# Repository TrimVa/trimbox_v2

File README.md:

# TrimBox

Enregistreur de télémétrie **GPS + inertiel** pour voitures radiocommandées,
avec **chronométrage au tour** affiché et annoncé sur la radio, **console web**
d'analyse et **mise à jour par Wi-Fi**. Construit autour d'un **ESP32-S3**.

> **État :** firmware **2.0-a17**, console **1.7.18**. Tout est écrit et testé
> sur PC, dans un navigateur et dans un émulateur ESP32-S3. **Essais sur le
> vrai matériel en cours** : GPS, IMU et script Lua sur la MT12 validés ; reste
> le roulage. Voir [les bancs d'essai](#bancs-dessai-à-la-réception-du-matériel).

---

## Sommaire

1. [Ce que fait le module](#ce-que-fait-le-module)
2. [Matériel](#matériel)
3. [Câblage](#câblage)
4. [Mise en route](#mise-en-route)
5. [Utilisation au bord de la piste](#utilisation-au-bord-de-la-piste)
6. [Console web](#console-web)
7. [Radio MT12 et script Lua](#radio-mt12-et-script-lua)
8. [Mises à jour du firmware](#mises-à-jour-du-firmware)
9. [Personnalisation](#personnalisation)
10. [Moniteur série et DEL](#moniteur-série-et-del)
11. [Sécurité et robustesse](#sécurité-et-robustesse)
12. [Dépannage](#dépannage)
13. [Contenu du dépôt](#contenu-du-dépôt)
14. [Compilation et tests automatiques](#compilation-et-tests-automatiques)
15. [Limites connues et suite du projet](#limites-connues-et-suite-du-projet)
16. [Documentation](#documentation)

---

## Ce que fait le module

| Fonction | Détail |
|---|---|
| **Enregistrement autonome** | GPS à 25 Hz + accéléromètre et gyroscope, sur la mémoire interne de 16 Mo. Aucun téléphone nécessaire pendant le roulage. |
| **Autonomie mémoire** | **01h42min à 25 Hz**, 02h08min à 20 Hz, 04h17min à 10 Hz, 08h34min à 5 Hz, 42h52min à 1 Hz (154 333 points). |
| **Enregistrement automatique** | l'enregistrement s'ouvre tout seul dès que la voiture roule et se ferme après 30 s à l'arrêt : **un roulage = une session**, sans rien toucher. Réglable, ou remplaçable par les boutons de la console. |
| **Filtres d'enregistrement** | attente du GPS, pause sans signal, extinction après inactivité. Rien n'est stocké au stand. |
| **Chrono embarqué** | calculé dans le module à 25 Hz, temps interpolés entre deux mesures (précision de l'ordre de la milliseconde). Mode **circuit** (une ligne, un temps par tour) ou **dragster** (départ + arrivée, chronos 0-30 / 0-50 / 0-80 km/h et 25 / 50 / 100 m). |
| **Pose de ligne depuis la radio** | voiture **arrêtée sur la ligne** : la commande arme la ligne, qui est posée dans le sens du départ dès que la voiture démarre (dans les 10 s) ; ce départ compte. Voiture **lancée** : la ligne est posée là où passe la voiture, perpendiculaire à sa trajectoire. Conservée d'une session à l'autre. |
| **Télémétrie radio** | position GPS, vitesse, état, et un message par tour (temps + écart au meilleur) vers la MT12, qui **annonce les temps à voix haute**. |
| **Console Bluetooth** | depuis la page GitHub du projet, sur Chrome Android. Comme le Wi-Fi, le Bluetooth se coupe quand la voiture roule et revient 30 s après l'arrêt. |
| **Console Wi-Fi** | le module ouvre son propre réseau quand la voiture est arrêtée depuis 30 s, et le coupe dès qu'elle roule. Fonctionne aussi sur **iPhone**, sans Internet. |
| **Analyse** | tracé coloré par vitesse, zoom, tours et parcours, forces G, temps en l'air, statistiques au survol du tracé, comparaison de sessions (portion choisie en glissant sur le profil, statistiques par session). Les **lignes posées depuis la radio** sont reprises d'office, et les **tours calculés en course** par le module s'affichent à côté de ceux de la console. |
| **Exports** | VBO (RaceChrono, Circuit Tools), CSV, GPX ; import de ces mêmes formats. |
| **Mise à jour Wi-Fi** | depuis le téléphone, avec retour automatique à la version précédente si la nouvelle ne démarre pas correctement. |

---

## Matériel

| Élément | Référence utilisée | Rôle |
|---|---|---|
| Carte | **NiceMCU « ESP32-S3_MINI_Nano » N16R8** | 16 Mo de flash, 8 Mo de PSRAM, Bluetooth, Wi-Fi, une prise USB-C |
| GPS | **HGLRC M100 Mini** (u-blox M10) | position et vitesse à 25 Hz |
| Centrale inertielle | module **LSM6DS3 / LSM6DS3TR-C** (I2C) | accélérations ±16 g, rotations ±2000 °/s |
| Récepteur | **RadioMaster ER5C-i** (ExpressLRS 2,4 GHz) | commande de la voiture + liaison CRSF avec le module |
| Radio | **RadioMaster MT12** (EdgeTX) | affichage du chrono, pose des lignes |
| ESC | **XC-E8** | aucune liaison : son port X-Bus est une entrée (voir ci-dessous) |
| Alimentation | régulateur abaisseur **5 V, ≥ 1 A** | depuis le BEC de l'ESC (6 à 8,4 V) |

Au banc, l'USB de la carte suffit à tout alimenter (à vérifier : la broche VIN
doit recevoir le 5 V de l'USB, sinon le GPS reste éteint).

⚠️ **Le module ne pilote jamais la voiture.** Direction et ESC restent sur
les sorties du récepteur : si le module plante, la voiture reste pilotable.

---

## Câblage

Schéma vectoriel : [SVG](docs/cablage-trimbox-s3.svg) · [PDF à imprimer](docs/cablage-trimbox-s3.pdf) (régénéré par `tools/gen_cablage.py`).

| Module | Broche du module | Carte (sérigraphie au dos) |
|---|---|---|
| **GPS M100 Mini** | V | **VIN** (5 V) |
| | G | GND |
| | T (TX) | **IO18** |
| | R (RX) | **IO17** |
| **IMU LSM6DS3** | VCC | **3V3** |
| | GND | GND |
| | SDA | **IO8** |
| | SCL | **IO9** |
| **Récepteur ER5C-i** | sortie 2 (Serial TX) | **IO16** |
| | sortie 3 (Serial RX) | **IO15** |
| | − | GND |
| **Alimentation (voiture)** | régulateur 5 V | **VIN** + GND |

**Boîtier imprimé 3D (1/10)** : [docs/boitier/trimbox-boitier.3mf](docs/boitier/trimbox-boitier.3mf),
sans aucune vis : carte clipsée dans le fond, GPS (antenne à l'air libre par
une ouverture) et IMU clipsés dans le couvercle, trou pour voir la DEL, dessous
plat pour adhésif double face + passants pour colliers. Mesures, impression et montage : [docs/boitier/LISEZMOI.md](docs/boitier/LISEZMOI.md).

Réglages du récepteur (interface web de l'ER5C-i, onglet *Model*) :
sorties 2 et 3 en **Serial TX / RX, protocole CRSF** ; direction sur la
sortie 1 (CH1) ; ESC sur la sortie 4 (**CH2**).

Règles à respecter :

- **Jamais plus de 3,3 V sur une broche GPIO** : l'ESP32-S3 ne tolère pas le 5 V.
- **Jamais le BEC (6 à 8,4 V) directement sur la broche VIN** de la carte :
  toujours passer par le régulateur 5 V.
- Broches à ne pas utiliser : IO33 à IO37 (mémoire PSRAM, bien que sorties sur la carte), 19 et 20 (USB),
  0, 3, 45, 46 (démarrage).
- L'IMU se visse **rigidement** sur le châssis, près du centre de gravité,
  axes alignés sur la voiture (pas sur mousse).

---

## Mise en route

Détail pas à pas : **[DEMARRAGE.md](DEMARRAGE.md)**. En résumé :

1. **Envoyer ce dépôt sur GitHub.** L'onglet **Actions** compile et teste
   tout seul (10 à 15 min la première fois).
2. **Activer GitHub Pages** (*Settings → Pages → branche `main`, dossier
   `/ (root)`*) pour la console Bluetooth en ligne.
3. **Premier flash, une seule fois, par câble depuis un ordinateur** :
   page **Releases** du dépôt → dernière version → `trimbox_s3-complet.bin`, avec
   https://espressif.github.io/esptool-js/ (Chrome ou Edge), adresse **0x0**,
   prise **USB** de la carte.
4. **Vérifier** : 30 s après la mise sous tension, le Wi-Fi
   `TrimBox-Buggy-1` apparaît (mot de passe `trimbox-rc`, à changer dans
   *Réglages → Véhicule et point d'accès*) ; http://192.168.4.1/
   affiche la console et la version du firmware en haut à droite.
5. **Radio** : copier `lua/trmbox.lua` sur la MT12 et régler le mixage de CH8
   ([lua/LISEZMOI.md](lua/LISEZMOI.md)).

---

## Utilisation au bord de la piste

1. **Brancher la batterie de la voiture.** Le module démarre toujours
   **enregistrement arrêté**.
2. **Rien à faire** : l'enregistrement démarre tout seul dès que la voiture
   roule (au-dessus du seuil d'arrêt, 5 km/h par défaut) et se ferme après
   30 s à l'arrêt. Chaque roulage donne une session. Les boutons *Démarrer*
   et *Arrêter* de la console restent disponibles, et la case **Démarrer et
   arrêter tout seul** permet de revenir à la commande manuelle.
3. **Rouler.** Le Wi-Fi **et le Bluetooth** du module se coupent dès que la
   voiture dépasse 7 km/h, pour ne pas gêner la radio ; ils reviennent seuls
   30 s après l'arrêt.
4. **Poser la ligne** (une fois par piste) : voiture **arrêtée sur la ligne**,
   sur la MT12 page *Lignes*, molette sur « Poser DEPART », **ENT**, puis
   **démarrer dans les 10 s** : la ligne est posée dans le sens du départ, et
   ce départ compte déjà. En roulant (> 7 km/h), la même commande pose la
   ligne tout de suite, là où passe la voiture.
5. **Chaque tour** : la radio annonce le temps ; double bip aigu avant
   l'annonce s'il s'agit du meilleur tour.
6. **Au stand** : 30 s après l'arrêt de la voiture, le Wi-Fi revient. Le
   téléphone s'y reconnecte, la console aussi : **télécharger** la session,
   analyser, exporter.

Mode **dragster** : poser aussi la ligne d'**arrivée** (« Poser ARRIVEE »).
Un temps par passage départ → arrivée, plus les chronos intermédiaires.

---

## Console web

Un seul fichier (`index.html`), sans aucune dépendance : elle fonctionne sans
réseau. Trois sources de données, au choix en haut de page :

| Source | Quand | Adresse |
|---|---|---|
| **Bluetooth** | Chrome sur Android, ordinateur | `https://<pseudo>.github.io/<dépôt>/` |
| **Wi-Fi** | tout téléphone, dont iPhone ; au stand | `http://192.168.4.1/` (Wi-Fi du module) |
| **Démo** | sans matériel, pour découvrir | `…/index.html?demo=1` |

Fonctions : données en direct, état de la mémoire, démarrage / arrêt et
réglages de l'enregistrement, téléchargement et effacement, analyse
(tracé, tours, dragster, G, sauts), comparaison, exports VBO / CSV / GPX,
mise à jour du firmware (en Wi-Fi), thème clair / sombre et **couleur
d'accent** au choix (bouton palette), installable comme une application
(PWA). L'en-tête affiche la version de la console et celle du firmware de la
carte connectée.

La mise en page s'adapte à l'écran : une colonne sur téléphone (dès 320 px),
une colonne plus large sur tablette. Sur ordinateur, la console occupe **toute
la largeur** avec des **onglets** *Appareil*, *Analyse*, *Sessions* et
*Réglages* ; dans chaque onglet, les panneaux se partagent la ligne.

**Fond satellite en Wi-Fi.** Le point d'accès de la TrimBox n'a pas
Internet : les images satellite passent par la **4G du téléphone**. Pour cela :

- sur Android, activez les **données mobiles quand le Wi-Fi n'a pas
  Internet** (option « Basculer vers les données mobiles » ou « Wi-Fi
  adaptatif », selon la marque) ;
- ouvrez la console dans **Chrome** (`http://192.168.4.1`), et non dans la
  fenêtre « Se connecter à TrimBox-… » qui s'ouvre toute seule : cette
  fenêtre est limitée au Wi-Fi, les images ne peuvent pas y arriver.

Sans réponse d'Internet, la console garde le fond satellite actif, affiche une
explication et réessaie toutes les 10 s : la carte apparaît dès que la 4G
répond. Le reste fonctionne à l'identique, et le téléchargement est bien plus
rapide qu'en Bluetooth. Sans réseau mobile, deux solutions :

- **après la séance** : télécharger la session (CSV / GPX / VBO), puis la
  rouvrir dans la console en ligne, avec *Ouvrir des enregistrements* ;
- **au bord de la piste** : utiliser la console en ligne connectée **par
  Bluetooth**.

**Voiture à l'arrêt.** Une voiture posée semble « dériver » de 1 à 3 m à cause
du bruit du GPS. Pour l'éviter, le firmware fige la position et met la
vitesse à 0 dès que la voiture est immobile :
- **quand** : vitesse sous 1,1 km/h pendant 0,2 s, sans mouvement vu par l'IMU ;
- **reprise** : dès que la vitesse dépasse 2,2 km/h, que l'IMU bouge, ou que la
  voiture s'est éloignée de 4 m ;
- **pour enregistrer le GPS brut** : `STILL_HOLD 0` dans `config.h`.

---

## Radio MT12 et script Lua

Script `lua/trmbox.lua` → carte SD de la radio, `SCRIPTS/TELEMETRY/`.
Mode d'emploi complet : **[lua/LISEZMOI.md](lua/LISEZMOI.md)**.

- **Page Chrono** : dernier tour en grand, numéro, écart, meilleur tour,
  tours précédents ; état du module, lignes posées, indicateur Wi-Fi.
- **Page Machine** : vitesse (0 sous 3 km/h), vitesse maximale, satellites,
  qualité de liaison, RSSI, altitude, **tension de la batterie** (capteur du
  récepteur) et **date et heure du GPS** en heure locale.
- **Page Lignes** : poser le départ, l'arrivée, effacer.
- **Mixage CH8, indispensable** : *Modèle → Mixeur → CH8*, source **MAX**,
  poids **GV9**, mode « ajouter ». Sans lui, aucune commande de pose ne part
  de la radio. La page *Lignes* affiche la valeur réelle de la voie (`CH8
  +0%`), qui doit passer à ±100 % pendant un envoi. Un inter 3 positions sur
  CH8 marche aussi sans le script (haut 0,5 s = départ, bas 0,5 à 3 s =
  arrivée, bas 3 s = effacement).
- **Réglage ExpressLRS** : *Telem Ratio* **1:16** ou plus fréquent, sinon
  des messages de tour peuvent manquer.
- **Annonces vocales** : « meilleur tour », le temps du tour, l'écart avec le
  tour précédent (« moins 0,35 », « plus 1,00 », « égal »), et les accusés
  de pose de ligne (« départ posé », « vitesse trop faible »…). Les nombres
  viennent du pack vocal de la radio ; les 12 mots du script sont fournis dans
  `lua/SOUNDS/trimbox/` (copier `lua/SOUNDS` à la racine de la carte SD). Ils
  ont été produits par `tools/sons/generer-voix.bat` avec la voix Azure du pack
  EdgeTX (liste : `tools/sons/liste-sons-mt12.csv`). Sans eux, des bips les
  remplacent. `tools/sons/generer-mot.bat` produit à la demande d'autres mots
  ou phrases avec la même voix (texte et nom demandés, écoute avant d'enregistrer).
- **Date et heure GPS** : le module envoie la trame CRSF `0x03` une fois par
  seconde. Il faut **ExpressLRS 4.1 ou plus récent** sur l'émetteur **et** sur
  le récepteur pour qu'elle soit relayée, et une version d'EdgeTX qui la
  décode : après *Découvrir les capteurs*, un capteur **`Date`** apparaît.
  Avec l'option *Ajuster l'horloge* de ce capteur, la radio se met à l'heure
  toute seule. Le script affiche l'heure locale (France par défaut, heure
  d'été automatique ; réglages `TZ_OFFSET` et `TZ_EU_DST`).

Messages envoyés à la radio (capteur `FM`) :

| Message | Sens |
|---|---|
| `L12 21.345+0.35` | tour 12 en 21,345 s, 0,35 s de plus que le meilleur |
| `S REC C` | état (REC / PAUSE / STOP / NOFIX) et lignes (C circuit, D dragster, - aucune) |
| `R 0-50 2.184` | chrono intermédiaire (dragster) |
| `K DEPART OK` | accusé de pose de ligne (ou `VIT FAIBLE`, `PAS DE FIX`, `EFFACE`) |
| `W WIFI ON` | Wi-Fi de la console allumé / coupé |
| `U MAJ OK` | étapes d'une mise à jour du firmware |

---

## Mises à jour du firmware

**Par Wi-Fi, sans ordinateur :**

1. Modifier le code dans GitHub (bouton crayon) et valider : la compilation
   repart seule.
2. Page **Releases** du dépôt → dernière version → `trimbox_s3-app.bin`
   (publiée automatiquement quand tout est vert et que `FIRMWARE_VER` a
   changé ; sinon *Actions* → compilation verte → artefact
   **firmware-s3-app**).
3. Voiture **et** enregistrement arrêtés : console Wi-Fi → **Mise à jour du
   firmware** → choisir le fichier → **Envoyer au module** (environ 10 s).
4. La console se reconnecte et affiche « ✓ Nouvelle version active ».

Filets de sécurité :

- mauvais fichier refusé avec un message clair (fichier « complet », .uf2
  de la v1, autre projet, image corrompue) ;
- l'ancienne version n'est jamais effacée pendant l'envoi ;
- la nouvelle version ne se **valide qu'après 15 s** de bon fonctionnement ;
  si elle plante ou se fige avant, le module **revient seul** à la
  précédente ;
- page de secours : http://192.168.4.1/update.

⚠️ `trimbox_s3/partitions.csv` ne doit **jamais** changer dans une mise à jour
Wi-Fi : la table de partitions ne se remplace que par câble.

---

## Personnalisation

Dans **`trimbox_s3/src/config.h`** :

| Réglage | Par défaut | Rôle |
|---|---|---|
| `DEVICE_NICKNAME` | `"Buggy 1"` | nom du véhicule **par défaut** (16 caractères max) : `TrimBox Buggy 1` en Bluetooth, `TrimBox-Buggy-1` en Wi-Fi ; se change ensuite dans la console |
| `WIFI_PASS` | `"trimbox-rc"` | mot de passe Wi-Fi **par défaut** (8 à 63 caractères) ; se change dans la console |
| `WIFI_AUTO_DEFAULT` | `1` | Wi-Fi automatique à l'arrêt (0 : seulement à la demande) |
| `WIFI_AUTO_ON_S` | `30` | secondes d'arrêt avant l'ouverture du Wi-Fi |
| `CRSF_LINE_CHANNEL_DEFAULT` | `8` | voie radio de pose de ligne |
| `PIN_LED_RGB` | `48` | DEL RGB de la carte (à confirmer : si elle reste éteinte, essayer 38 ou 21) |
| `AXIS_*` | capteur à plat, x vers l'avant | orientation de l'IMU selon son montage |

Les autres valeurs du fichier ont été fixées par mesure ou par contrainte
matérielle : ne pas les modifier sans raison (voir les cahiers des charges).

Plusieurs voitures : un nom de véhicule différent par module suffit à les
distinguer (Bluetooth, Wi-Fi et console). Il se change dans la console,
*Réglages → Véhicule et point d'accès*, sans recompiler.

---

## Moniteur série et DEL

Moniteur série à **115 200 bauds**, sur la prise **USB** de la carte
(onglet *Console* d'esptool-js, moniteur de l'IDE Arduino, PuTTY…) :

| Touche | Effet |
|---|---|
| `s` | arrêt d'urgence de l'enregistrement |
| `r` | démarrer l'enregistrement (essai sans téléphone) |
| `w` | Wi-Fi marche / arrêt |
| `i` | état : mémoire, enregistrement, configuration, lignes |
| `b` | banc d'essai : cadence GPS, IMU, radio, Bluetooth, Wi-Fi, partition du firmware |
| `m` | mesures de la centrale inertielle en direct (10 lignes, mg et c°/s) |
| `z` | configuration par défaut (données conservées) |
| `x` | nom du véhicule et mot de passe Wi-Fi d'origine (mot de passe oublié) |
| `?` | aide |

**Bouton BOOT**, appui long de 3 s : Wi-Fi marche / arrêt.

**DEL de la carte :**

| Couleur | Sens |
|---|---|
| rouge clignotant | GPS ou mémoire absents (normal au banc sans GPS) |
| rouge fixe | enregistrement en cours |
| orange | enregistrement en pause |
| vert clignotant | GPS calé, prêt |
| bleu fixe | console connectée |
| bleu clignotant | Wi-Fi ouvert, en attente du téléphone |

Les couleurs se superposent : rouge + bleu = violet (enregistrement en cours, console connectée).

---

## Sécurité et robustesse

- **Coupure d'alimentation** (batterie arrachée en pleine session) : les
  données déjà enregistrées restent intactes et téléchargeables ; la
  configuration est écrite en double exemplaire ; l'enregistrement **ne
  reprend jamais tout seul** au redémarrage ; les points incomplets sont
  écartés à la lecture.
- **Effacement de la mémoire** : impossible pendant un enregistrement, et
  non annulable une fois lancé (il ne dure que quelques secondes).
- **Wi-Fi et Bluetooth coupés en roulant**, quel que soit le réglage : la
  liaison de commande 2,4 GHz passe avant la console. Rallumage automatique
  après 30 s d'arrêt (`BLE_AUTO_OFF 0` dans `config.h` pour garder le
  Bluetooth en permanence).
- **Chien de garde** : si le programme se fige plus de 5 s, la carte
  redémarre seule.
- **Protocole** : trames avec somme de contrôle, réassemblage tolérant aux
  pertes ; une trame corrompue ne peut pas produire de valeurs absurdes
  dans l'analyse.

---

## Dépannage

| Problème | Piste |
|---|---|
| Carte non détectée pour le flash | câble de **données**, prise **USB** ; BOOT maintenu + RST, relâcher BOOT |
| Pas de Wi-Fi `TrimBox-…` | attendre 30 s voiture arrêtée ; appui long BOOT ; touche `w` ; vérifier le journal série |
| « Pas d'accès Internet » sur le téléphone | normal : rester connecté et ouvrir http://192.168.4.1/ |
| `[gnss] AUCUNE RÉPONSE` | TX et RX croisés (GPS TX → GPIO 18), alimentation 5 V |
| GPS à moins de 25 Hz | normal à l'intérieur ; si Galileo est coupé tout seul, le noter (réglage automatique) |
| `[imu] ABSENTE` | SDA = 8, SCL = 9, 3,3 V, masse |
| Radio : « PAS DE LIAISON » | récepteur : sorties 2/3 en CRSF, TX/RX croisés ; *Découvrir les capteurs* sur la MT12 |
| Des tours manquent sur la radio | *Telem Ratio* ExpressLRS trop bas : 1:16 ou plus fréquent |
| Rien ne se passe à la pose de ligne (la page *Lignes* affiche `CH8 +0%`) | mixage CH8 absent : *Modèle → Mixeur → CH8*, source MAX, poids GV9, mode Ajouter |
| « délai dépassé » après une pose à l'arrêt | démarrer dans les 10 s qui suivent la commande |
| Mise à jour refusée | lire le message : enregistrement en cours, mauvais fichier, voiture en mouvement |
| Console : ancienne version affichée | recharger la page ; en Bluetooth, vider le cache du navigateur |
| La compilation GitHub échoue | ouvrir l'étape en rouge dans *Actions* ; le premier test en échec indique la cause |

---

## Contenu du dépôt

```
trimbox_s3/                      firmware ESP32-S3 (croquis Arduino)
│   trimbox_s3.ino               point d'entrée
│   partitions.csv               table de partitions 16 Mo — NE PAS MODIFIER
│   LISEZMOI.md                  câblage, premier flash, bancs d'essai
└── src/
    ├── config.h                 réglages et brochage
    ├── app.cpp                  boucle principale, commandes, chrono, Wi-Fi auto
    ├── console_gz.h             console intégrée (générée, ne pas éditer)
    ├── core/                    logique SANS matériel, testée sur PC :
    │                            protocoles (TrimBox, UBX, CRSF), chrono,
    │                            automate d'enregistrement, pose de ligne,
    │                            configuration A/B, serveur HTTP/WebSocket,
    │                            contrôle des mises à jour
    └── hw/                      pilotes : GPS, IMU, mémoire, Bluetooth,
                                 Wi-Fi, radio, mise à jour
lua/trmbox.lua                   script de télémétrie MT12 (+ LISEZMOI.md)
lua/SOUNDS/trimbox/              les 12 mots des annonces vocales (à copier sur la carte SD)
index.html                       console web (GitHub Pages et firmware)
trimbox-sw.js                    service worker (console hors ligne)
trimbox-diy-console-demo.html    redirection des anciens liens vers la démo
tools/embed_console.py           intègre index.html au firmware
tools/gen_cablage.py             génère le schéma de câblage (docs/)
tools/gen_boitier.py             génère le boîtier imprimé 3D (docs/boitier/)
tools/imu_test/                  croquis de test de la centrale inertielle seule
docs/                            schéma de câblage (SVG, PDF) et boîtier 3D
tools/sons/                      sons de la radio : liste (CSV) + génération Azure des mots du script
tools/xbus_probe/                sonde ESP32 du port X-Bus (piste close)
tests/native/                    tests de la logique (g++) + comparaison avec la console
tests/web/                       console dans un navigateur, avec le serveur du firmware
tests/lua/                       script Lua avec l'API EdgeTX simulée
tests/qemu/                      firmware complet dans l'émulateur ESP32-S3
.github/workflows/build-s3.yml   compilation et tests à chaque envoi
CAHIER-DES-CHARGES.md            spécification complète (matériel, protocole, firmware, radio, console, pièges)
trimbox-etat-projet.json         état du projet, pour reprendre avec une IA
REPRISE-IA.md                    marche à suivre pour reprendre le développement avec une IA
```

---

## Compilation et tests automatiques

À chaque envoi sur GitHub, l'onglet **Actions** enchaîne :

| Étape | Vérifie |
|---|---|
| Tests natifs | protocoles, chrono (bancs v1 : 5 tours de 20,00 s, ligne en 4 endroits ; dragster à 6 m/s²), automate d'enregistrement, pose de ligne, configuration A/B, serveur web, contrôles de mise à jour — plus de 950 vérifications |
| Chrono firmware = console | les mêmes trajets rejoués dans les deux : écart maximal 1 ms |
| Script Lua | messages, sons, impulsions GV9, affichage (API EdgeTX simulée) |
| Compilation | ESP32-S3, core `esp32:esp32@3.3.12`, NimBLE-Arduino 2.5.1 (versions figées) |
| Console dans un navigateur | chargement, connexion Wi-Fi, direct, téléchargement, reconnexion, couleur, envoi du firmware compilé |
| Émulateur | Wi-Fi automatique à l'arrêt, pose de ligne par le script Lua, tours de 12,000 s reçus sans perte, coupure d'alimentation, retour arrière après une mise à jour qui plante |

Artefacts produits :

| Artefact | Contenu | Usage |
|---|---|---|
| `firmware-s3-complet` | `trimbox_s3-complet.bin` (+ fichiers séparés) | premier flash, par câble, adresse 0x0 |
| `firmware-s3-app` | `trimbox_s3-app.bin` | mise à jour par Wi-Fi |
| `capture-console-wifi` | capture d'écran | contrôle visuel de la console |

Il faut être **connecté à GitHub** pour télécharger un artefact.

**Release automatique** : sur la branche `main`, quand tous les jobs sont
verts et que `FIRMWARE_VER` (`trimbox_s3/src/config.h`) n'a pas encore été
publiée, le job *Publication* crée la release `firmware-<version>` : les deux
`.bin`, bootloader et partitions séparés, la console `index.html`, le pack
radio `trimbox-radio.zip`, `SHA256SUMS.txt`, et des notes complètes (usage de
chaque fichier, procédures, nouveautés depuis la release précédente,
empreintes). Téléchargeable **sans compte GitHub**. Une version déjà publiée
n'est jamais écrasée : incrémenter `FIRMWARE_VER` pour publier.

---

## Limites connues et suite du projet

- **Essais matériels en cours** : GPS validé sur la carte (fix 3D,
  13 satellites, ~20 Hz), IMU validée avec `tools/imu_test` (|a| = 0,99 g au
  repos), script Lua validé sur la MT12 (affichage, tours, annonces vocales,
  accusés de pose). Restent à valider : mixage CH8 et pose de ligne depuis la
  radio, enregistrement automatique et chrono en roulage, Bluetooth et Wi-Fi
  en conditions réelles, boîtier imprimé.
- **ESC XC-E8, abandonné** : son port X-Bus (paramètre *PLine* de
  l'application) est une **entrée**. Analyseur logique et sonde ESP32 l'ont
  confirmé : ligne tenue en haut par une résistance de tirage, aucune
  émission, aucune réponse à une poignée de main. Les autres choix de *PLine*
  (Max.Brake, Max.Rev, Acc, DragBrake) sont eux aussi des entrées, et
  *ProtocolId* n'est qu'un numéro d'appareil sur le bus. Il n'y a donc pas de
  télémétrie à lire sur cette prise. La tension de batterie remonte déjà par
  la radio. Détail des essais : cahier des charges §13.
- **Batterie** : la tension s'affiche sur la radio (capteur du récepteur), pas
  dans la console (octet batterie toujours à 0).
- **Premier flash** : nécessite un ordinateur, une seule fois.

### Bancs d'essai à la réception du matériel

Dans l'ordre, en notant la sortie de la touche `b` à chaque étape
(détail dans [trimbox_s3/LISEZMOI.md](trimbox_s3/LISEZMOI.md)) :

1. carte seule : démarrage, mémoire, Wi-Fi, console ;
2. + GPS, dehors : 25 Hz — ✅ fix 3D, 13 satellites, ~20 Hz ;
3. + IMU : capteur reconnu — ✅ avec `tools/imu_test` ;
4. + récepteur : liaison CRSF, capteurs découverts sur la MT12 — ✅ messages
   du chrono reçus par le script Lua ;
5. console : connexion, enregistrement, téléchargement, effacement ;
6. roulage : pose de ligne, tours sur la radio, comparaison avec la console.

---

## Documentation

| Document | Contenu |
|---|---|
| [DEMARRAGE.md](DEMARRAGE.md) | mise en ligne, premier flash, mises à jour |
| [trimbox_s3/LISEZMOI.md](trimbox_s3/LISEZMOI.md) | câblage, flash, moniteur série, bancs d'essai |
| [lua/LISEZMOI.md](lua/LISEZMOI.md) | installation du script, mixage, utilisation |
| [CAHIER-DES-CHARGES.md](CAHIER-DES-CHARGES.md) | spécification complète du projet : matériel, protocole, firmware, radio, Wi-Fi et Bluetooth, mise à jour, console, script Lua, tests, **règles dures (§0)** et **pièges connus (§12)** |
| [trimbox-etat-projet.json](trimbox-etat-projet.json) | état du projet, à fournir à une IA pour reprendre le travail |
| [REPRISE-IA.md](REPRISE-IA.md) | marche à suivre et texte à coller pour reprendre avec une IA |

Le format de trame dérive de la documentation du protocole BLE RaceBox
(révision 8). Aucune compatibilité avec l'application RaceBox officielle n'est
recherchée.

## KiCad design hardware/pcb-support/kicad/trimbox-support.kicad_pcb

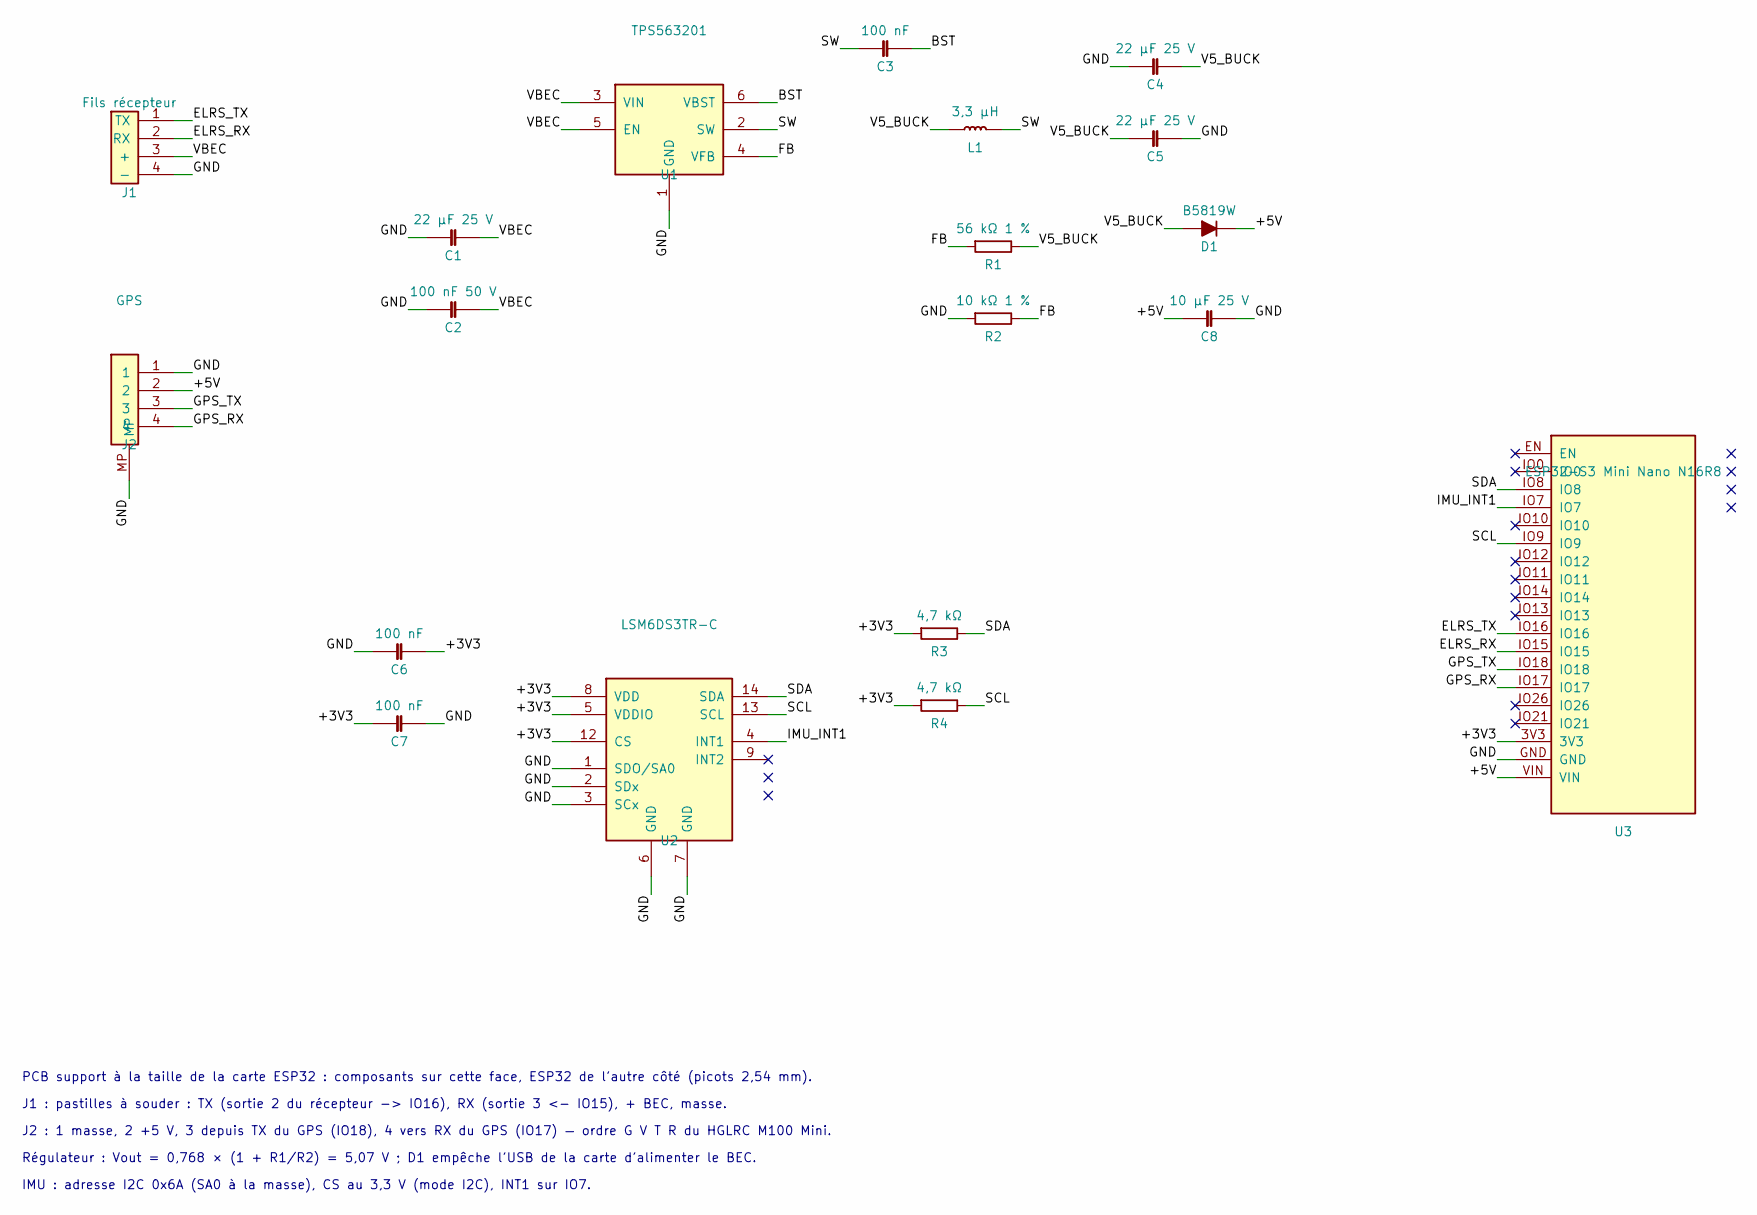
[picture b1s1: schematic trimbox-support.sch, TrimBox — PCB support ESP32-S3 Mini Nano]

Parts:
C1, C4, C5: 22 µF 25 V; C_0805_2012Metric; MPN CL21A226MAQNNNE; LCSC C45783
C2: 100 nF 50 V; C_0603_1608Metric; MPN CC0603KRX7R9BB104; LCSC C14663
C3, C6, C7: 100 nF; C_0402_1005Metric; MPN CL05B104KO5NNNC; LCSC C1525
C8: 10 µF 25 V; C_0805_2012Metric; MPN CL21A106KAYNNNE; LCSC C15850
D1: B5819W; D_SOD-123; MPN B5819W; LCSC C8598
J1: Fils récepteur; TrimBox_Pastilles_fils_4x1.1mm; MPN Pastilles à souder
J2: GPS; JST_SH_SM04B-SRSS-TB_1x04-1MP_P1.00mm_Horizontal; MPN SM04B-SRSS-TB(LF)(SN); LCSC C160404
L1: 3,3 µH; L_Taiyo-Yuden_NR-30xx; MPN FNR3015S3R3MT; LCSC C167749
R1: 56 kΩ 1 %; R_0402_1005Metric; MPN 0402WGF5602TCE; LCSC C25796
R2: 10 kΩ 1 %; R_0402_1005Metric; MPN 0402WGF1002TCE; LCSC C25744
R3, R4: 4,7 kΩ; R_0402_1005Metric; MPN 0402WGF4701TCE; LCSC C25900
U1: TPS563201; SOT-23-6; MPN TPS563201DDCR; LCSC C116592
U2: LSM6DS3TR-C; LGA-14_3x2.5mm_P0.5mm_LayoutBorder3x4y; MPN LSM6DS3TR-C; LCSC C967633
U3: ESP32-S3 Mini Nano N16R8; TrimBox_ESP32-S3_MiniNano_Carrier

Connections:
+3V3: C6.2, C7.1, R3.1, R4.1, U2.5 (VDDIO), U2.8 (VDD), U2.12 (CS), U3.3V3
+5V: C8.1, D1.1 (K), J2.2, U3.VIN
BST: C3.2, U1.6 (VBST)
ELRS_RX: J1.2 (RX), U3.IO15
ELRS_TX: J1.1 (TX), U3.IO16
FB: R1.1, R2.2, U1.4 (VFB)
GND: C1.1, C2.1, C4.1, C5.2, C6.1, C7.2, C8.2, J1.4 (-), J2.1, J2.MP, R2.1, U1.1 (GND), U2.1 (SDO/SA0), U2.2 (SDx), U2.3 (SCx), U2.6 (GND), U2.7 (GND), U3.GND
GPS_RX: J2.4, U3.IO17
GPS_TX: J2.3, U3.IO18
IMU_INT1: U2.4 (INT1), U3.IO7
SCL: R4.2, U2.13 (SCL), U3.IO9
SDA: R3.2, U2.14 (SDA), U3.IO8
SW: C3.1, L1.2, U1.2 (SW)
V5_BUCK: C4.2, C5.1, D1.2 (A), L1.1, R1.2
VBEC: C1.2, C2.2, J1.3 (+), U1.3 (VIN), U1.5 (EN)

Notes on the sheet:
PCB support à la taille de la carte ESP32 : composants sur cette face, ESP32 de l'autre côté (picots 2,54 mm).
J1 : pastilles à souder : TX (sortie 2 du récepteur -> IO16), RX (sortie 3 <- IO15), + BEC, masse.
J2 : 1 masse, 2 +5 V, 3 depuis TX du GPS (IO18), 4 vers RX du GPS (IO17) — ordre G V T R du HGLRC M100 Mini.
Régulateur : Vout = 0,768 × (1 + R1/R2) = 5,07 V ; D1 empêche l'USB de la carte d'alimenter le BEC.
IMU : adresse I2C 0x6A (SA0 à la masse), CS au 3,3 V (mode I2C), INT1 sur IO7.

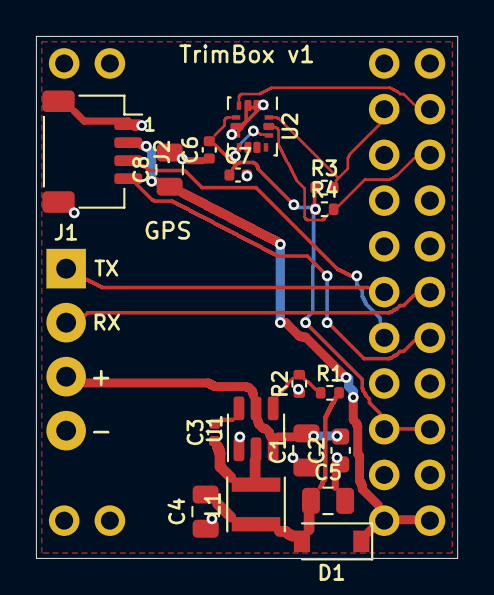
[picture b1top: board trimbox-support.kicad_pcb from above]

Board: 2 copper layers, 23.4 x 29.0 mm, 19 parts (0 on the bottom side), 15 nets.
